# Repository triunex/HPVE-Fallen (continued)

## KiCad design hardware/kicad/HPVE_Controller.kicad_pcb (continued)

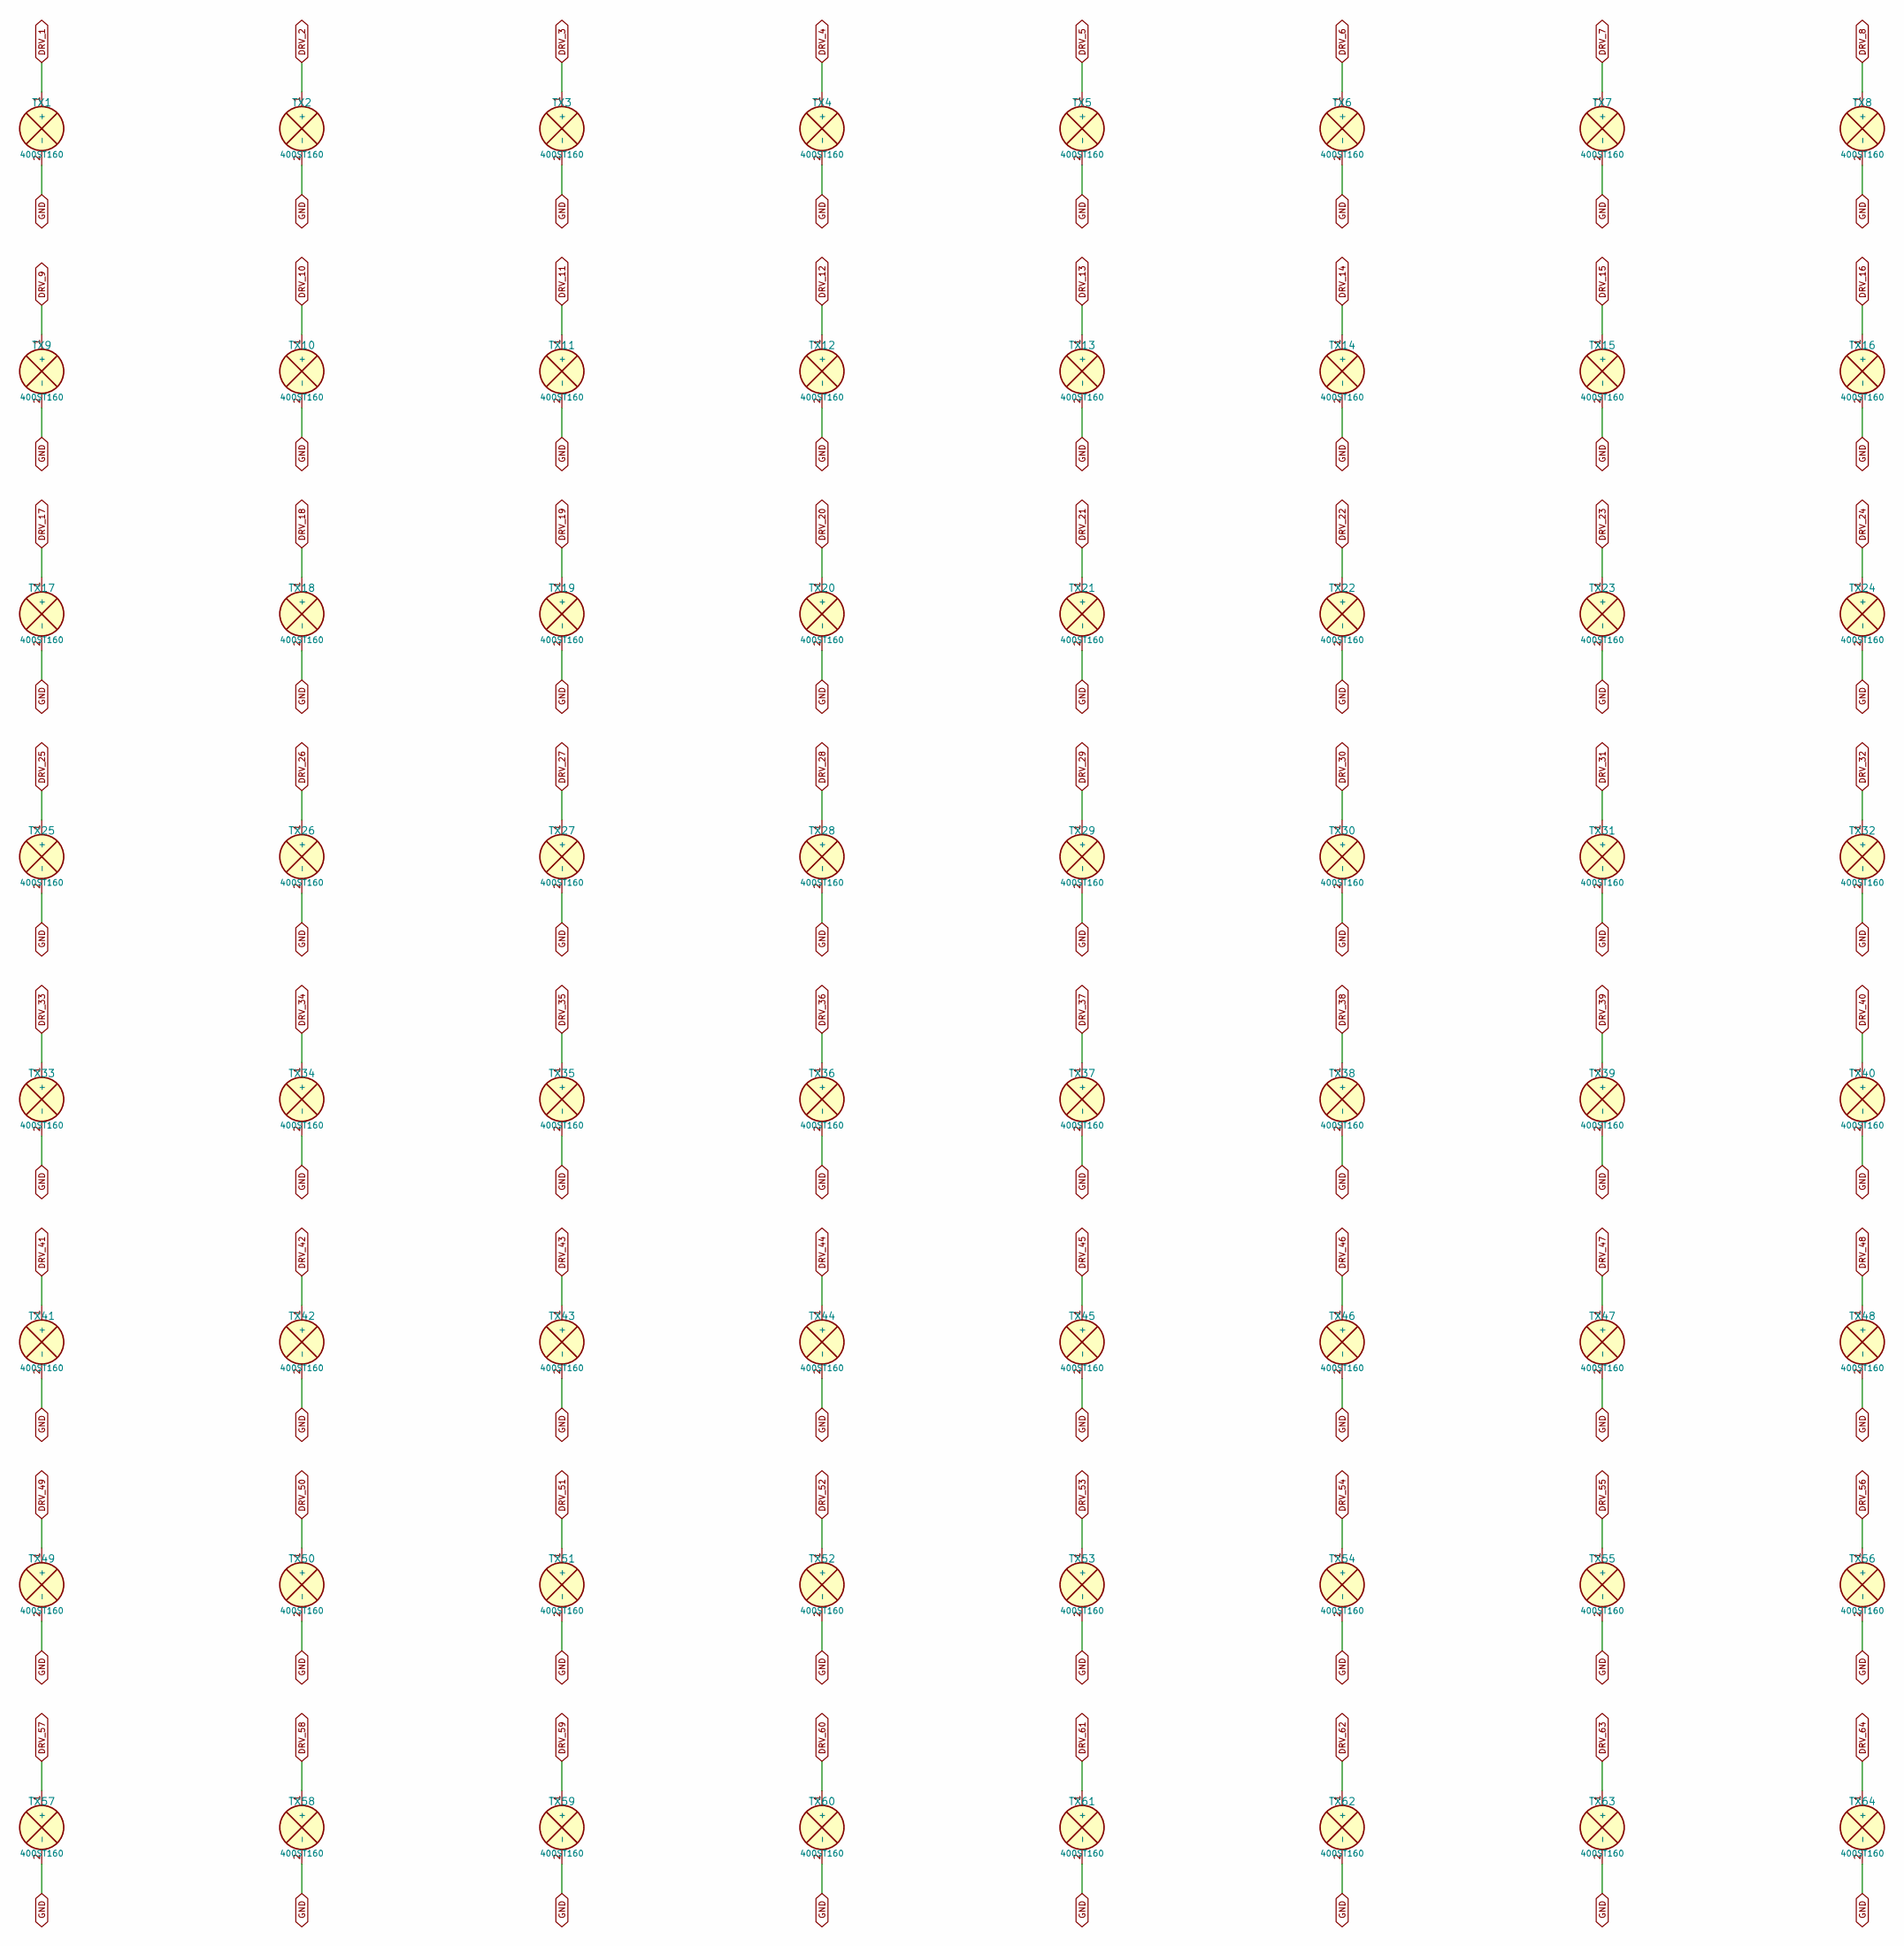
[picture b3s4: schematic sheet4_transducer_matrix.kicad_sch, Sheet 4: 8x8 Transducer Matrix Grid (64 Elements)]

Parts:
TX1, TX2, TX3, TX4, TX5, TX6, TX7, TX8, TX9, TX10, TX11, TX12, TX13, TX14, TX15, TX16, TX17, TX18, TX19, TX20, TX21, TX22, TX23, TX24, TX25, TX26, TX27, TX28, TX29, TX30, TX31, TX32, TX33, TX34, TX35, TX36, TX37, TX38, TX39, TX40, TX41, TX42, TX43, TX44, TX45, TX46, TX47, TX48, TX49, TX50, TX51, TX52, TX53, TX54, TX55, TX56, TX57, TX58, TX59, TX60, TX61, TX62, TX63, TX64: 400ST160; PinHeader_1x02_P2.54mm_Vertical

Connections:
DRV_1: TX1.1 (+); also elsewhere on the board
DRV_2: TX2.1 (+); also elsewhere on the board
DRV_3: TX3.1 (+); also elsewhere on the board
DRV_4: TX4.1 (+); also elsewhere on the board
DRV_5: TX5.1 (+); also elsewhere on the board
DRV_6: TX6.1 (+); also elsewhere on the board
DRV_7: TX7.1 (+); also elsewhere on the board
DRV_8: TX8.1 (+); also elsewhere on the board
DRV_9: TX9.1 (+); also elsewhere on the board
DRV_10: TX10.1 (+); also elsewhere on the board
DRV_11: TX11.1 (+); also elsewhere on the board
DRV_12: TX12.1 (+); also elsewhere on the board
DRV_13: TX13.1 (+); also elsewhere on the board
DRV_14: TX14.1 (+); also elsewhere on the board
DRV_15: TX15.1 (+); also elsewhere on the board
DRV_16: TX16.1 (+); also elsewhere on the board
DRV_17: TX17.1 (+); also elsewhere on the board
DRV_18: TX18.1 (+); also elsewhere on the board
DRV_19: TX19.1 (+); also elsewhere on the board
DRV_20: TX20.1 (+); also elsewhere on the board
DRV_21: TX21.1 (+); also elsewhere on the board
DRV_22: TX22.1 (+); also elsewhere on the board
DRV_23: TX23.1 (+); also elsewhere on the board
DRV_24: TX24.1 (+); also elsewhere on the board
DRV_25: TX25.1 (+); also elsewhere on the board
DRV_26: TX26.1 (+); also elsewhere on the board
DRV_27: TX27.1 (+); also elsewhere on the board
DRV_28: TX28.1 (+); also elsewhere on the board
DRV_29: TX29.1 (+); also elsewhere on the board
DRV_30: TX30.1 (+); also elsewhere on the board
DRV_31: TX31.1 (+); also elsewhere on the board
DRV_32: TX32.1 (+); also elsewhere on the board
DRV_33: TX33.1 (+); also elsewhere on the board
DRV_34: TX34.1 (+); also elsewhere on the board
DRV_35: TX35.1 (+); also elsewhere on the board
DRV_36: TX36.1 (+); also elsewhere on the board
DRV_37: TX37.1 (+); also elsewhere on the board
DRV_38: TX38.1 (+); also elsewhere on the board
DRV_39: TX39.1 (+); also elsewhere on the board
DRV_40: TX40.1 (+); also elsewhere on the board
DRV_41: TX41.1 (+); also elsewhere on the board
DRV_42: TX42.1 (+); also elsewhere on the board
DRV_43: TX43.1 (+); also elsewhere on the board
DRV_44: TX44.1 (+); also elsewhere on the board
DRV_45: TX45.1 (+); also elsewhere on the board
DRV_46: TX46.1 (+); also elsewhere on the board
DRV_47: TX47.1 (+); also elsewhere on the board
DRV_48: TX48.1 (+); also elsewhere on the board
DRV_49: TX49.1 (+); also elsewhere on the board
DRV_50: TX50.1 (+); also elsewhere on the board
DRV_51: TX51.1 (+); also elsewhere on the board
DRV_52: TX52.1 (+); also elsewhere on the board
DRV_53: TX53.1 (+); also elsewhere on the board
DRV_54: TX54.1 (+); also elsewhere on the board
DRV_55: TX55.1 (+); also elsewhere on the board
DRV_56: TX56.1 (+); also elsewhere on the board
DRV_57: TX57.1 (+); also elsewhere on the board
DRV_58: TX58.1 (+); also elsewhere on the board
DRV_59: TX59.1 (+); also elsewhere on the board
DRV_60: TX60.1 (+); also elsewhere on the board
DRV_61: TX61.1 (+); also elsewhere on the board
DRV_62: TX62.1 (+); also elsewhere on the board
DRV_63: TX63.1 (+); also elsewhere on the board
DRV_64: TX64.1 (+); also elsewhere on the board
GND: TX1.2 (-), TX2.2 (-), TX3.2 (-), TX4.2 (-), TX5.2 (-), TX6.2 (-), TX7.2 (-), TX8.2 (-), TX9.2 (-), TX10.2 (-), TX11.2 (-), TX12.2 (-), TX13.2 (-), TX14.2 (-), TX15.2 (-), TX16.2 (-), TX17.2 (-), TX18.2 (-), TX19.2 (-), TX20.2 (-), TX21.2 (-), TX22.2 (-), TX23.2 (-), TX24.2 (-), TX25.2 (-), TX26.2 (-), TX27.2 (-), TX28.2 (-), TX29.2 (-), TX30.2 (-), TX31.2 (-), TX32.2 (-), TX33.2 (-), TX34.2 (-), TX35.2 (-), TX36.2 (-), TX37.2 (-), TX38.2 (-), TX39.2 (-), TX40.2 (-), TX41.2 (-), TX42.2 (-), TX43.2 (-), TX44.2 (-), TX45.2 (-), TX46.2 (-), TX47.2 (-), TX48.2 (-), TX49.2 (-), TX50.2 (-), TX51.2 (-), TX52.2 (-), TX53.2 (-), TX54.2 (-), TX55.2 (-), TX56.2 (-), TX57.2 (-), TX58.2 (-), TX59.2 (-), TX60.2 (-), TX61.2 (-), TX62.2 (-), TX63.2 (-), TX64.2 (-); also elsewhere on the board

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
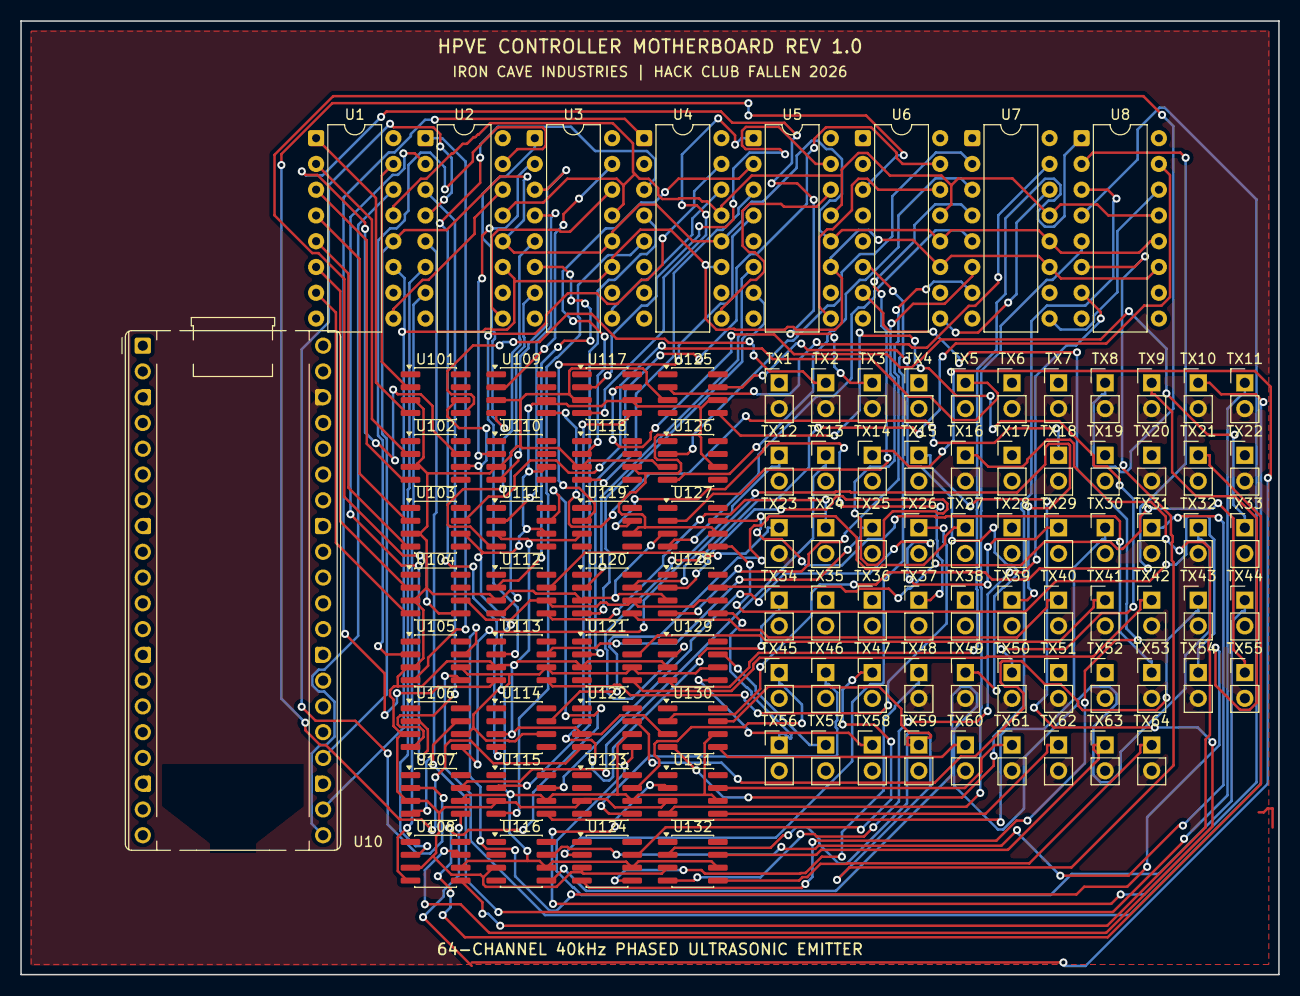
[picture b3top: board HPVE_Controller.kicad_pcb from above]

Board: 2 copper layers, 124.0 x 94.0 mm, 105 parts (0 on the bottom side), 142 nets.

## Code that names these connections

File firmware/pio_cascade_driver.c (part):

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/*
 * Exact Hardware Netlist Mapping for HPVE_Tile_16Ch:
 * - Each tile has 2x 74HC595:
 *   U1 (receives J_IN Pin 4 SPI_MOSI_IN): Q0..Q7 -> SIG_1..SIG_8   -> TX1..TX8
 *   U2 (receives U1 Pin 9 QH' cascade):   Q0..Q7 -> SIG_9..SIG_16  -> TX9..TX16
 *   U2 Pin 9 QH' -> J_OUT Pin 4 SPI_MOSI_OUT -> next tile J_IN Pin 4.
 *
 * - In a 4-tile daisy chain (Tile 0 -> Tile 1 -> Tile 2 -> Tile 3):
 *   64 clock pulses per slice shift 64 bits out of PIO MSB-first (two 32-bit OSR words).
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    gpio_set_dir(PIN_DRV_OE, GPIO_OUT);
    gpio_put(PIN_DRV_OE, 1);

    gpio_init(PIN_SYNC_TRIG);
    gpio_set_dir(PIN_SYNC_TRIG, GPIO_OUT);
    gpio_put(PIN_SYNC_TRIG, 0);

    gpio_init(PIN_STATUS_LED);
    gpio_set_dir(PIN_STATUS_LED, GPIO_OUT);
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        g_pio_inst,
        g_pio_sm,
        g_pio_offset,
        PIN_SPI_MOSI,
        PIN_SPI_SCK,
        clkdiv,
        shift_bits,
        pad_cycles
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
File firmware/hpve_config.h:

#ifndef HPVE_CONFIG_H
#define HPVE_CONFIG_H

#include <stdint.h>
#include <stdbool.h>
#include <stddef.h>

#ifdef __cplusplus
extern "C" {
#endif

#define HPVE_FW_VERSION_MAJOR       2
#define HPVE_FW_VERSION_MINOR       7
#define HPVE_FW_VERSION_PATCH       0

#define SYS_CLOCK_KHZ               128000u
#define SYS_CLOCK_HZ                128000000u
#define PIO_CLKDIV_INT              1u
#define PIO_CLKDIV_FRAC             64u
#define PIO_CLOCK_HZ                102400000u

#define ACOUSTIC_CARRIER_HZ         40000u
#define ACOUSTIC_PERIOD_US          25u
#define SOUND_SPEED_MPS             343.0f
#define ACOUSTIC_WAVELENGTH_M       0.008575f
#define ACOUSTIC_WAVENUMBER_K       732.73298f

#define TILE_GRID_COLS              4u
#define TILE_GRID_ROWS              4u
#define TILE_CHANNELS               16u
#define MAX_CASCADE_TILES           4u
#define NUM_TRANSDUCERS             (TILE_CHANNELS * MAX_CASCADE_TILES)
#define GLOBAL_GRID_COLS            8u
#define GLOBAL_GRID_ROWS            8u

#define TRANSDUCER_PITCH_M          0.0165f
#define TRANSDUCER_CAN_DIAM_M       0.0162f
#define TRANSDUCER_LEAD_PITCH_M     0.0100f
#define TILE_SPAN_M                 (TILE_GRID_COLS * TRANSDUCER_PITCH_M)
#define ARRAY_SPAN_X_M              (GLOBAL_GRID_COLS * TRANSDUCER_PITCH_M)
#define ARRAY_SPAN_Y_M              (GLOBAL_GRID_ROWS * TRANSDUCER_PITCH_M)

#define NUM_PHASE_STEPS             16u
#define PHASE_STEP_MASK             (NUM_PHASE_STEPS - 1u)
#define WORDS_PER_SLICE             2u
#define SLICES_PER_CARRIER_PERIOD   NUM_PHASE_STEPS
#define CARRIER_CYCLES_PER_FRAME    200u
#define SLICES_PER_DMA_FRAME        (SLICES_PER_CARRIER_PERIOD * CARRIER_CYCLES_PER_FRAME)
#define WORDS_PER_DMA_FRAME         (SLICES_PER_DMA_FRAME * WORDS_PER_SLICE)

#define PIO_CYCLES_PER_CARRIER      2560u
#define PIO_CYCLES_PER_SLICE        (PIO_CYCLES_PER_CARRIER / NUM_PHASE_STEPS)
#define PIO_SHIFT_BITS_PER_SLICE    64u

#define HAPTIC_MOD_FREQ_HZ          200u
#define HAPTIC_CARRIER_RATIO        (ACOUSTIC_CARRIER_HZ / HAPTIC_MOD_FREQ_HZ)

#define MAX_MULTIFOCAL_NODES        7u
#define TRAJ_HISTORY_LEN            32u

#define PIN_I2C_SDA                 0u
#define PIN_I2C_SCL                 1u
#define PIN_SPI_MOSI                2u
#define PIN_SPI_SCK                 3u
#define PIN_SPI_LATCH               4u
#define PIN_DRV_OE                  5u
#define PIN_PHOTONIC_R              6u
#define PIN_PHOTONIC_G              7u
#define PIN_PHOTONIC_B              8u
#define PIN_SYNC_TRIG               9u
#define PIN_ENC_X_A                 10u
#define PIN_ENC_X_B                 11u
#define PIN_ENC_Y_A                 12u
#define PIN_ENC_Y_B                 13u
#define PIN_ENC_Z_A                 14u
#define PIN_ENC_Z_B                 15u
#define PIN_BTN_MODE                16u
#define PIN_BTN_ENABLE              17u
#define PIN_STATUS_LED              25u

#define WORKSPACE_MIN_X_M          -0.060f
#define WORKSPACE_MAX_X_M           0.060f
#define WORKSPACE_MIN_Y_M          -0.060f
#define WORKSPACE_MAX_Y_M           0.060f
#define WORKSPACE_MIN_Z_M           0.015f
#define WORKSPACE_MAX_Z_M           0.140f
#define WORKSPACE_DEFAULT_Z_M       0.055f

#define Q16_SHIFT                   16
#define Q16_ONE                     (1 << Q16_SHIFT)
#define Q16_HALF                    (1 << (Q16_SHIFT - 1))
#define FLOAT_TO_Q16(x)             ((int32_t)((x) * (float)Q16_ONE))
#define Q16_TO_FLOAT(x)             ((float)(x) / (float)Q16_ONE)
#define Q16_MUL(a, b)               ((int32_t)(((int64_t)(a) * (int64_t)(b)) >> Q16_SHIFT))
#define Q16_DIV(a, b)               ((int32_t)((((int64_t)(a)) << Q16_SHIFT) / (b)))

typedef int32_t q16_t;

typedef enum {
    HPVE_MODE_STANDBY         = 0,
    HPVE_MODE_TWIN_TRAP       = 1,
    HPVE_MODE_BOTTLE_TRAP     = 2,
    HPVE_MODE_VORTEX_BEAM     = 3,
    HPVE_MODE_HAPTIC_FOCUS    = 4,
    HPVE_MODE_VOLUMETRIC_POV  = 5,
    HPVE_MODE_DUAL_TRAP_SMF   = 6,
    HPVE_MODE_ARC_REACTOR_SMF = 7,
    HPVE_MODE_COUNT           = 8
} hpve_mode_t;

typedef enum {
    TRAJ_NONE_STATIC            = 0,
    TRAJ_ARC_REACTOR_CORE       = 1,
    TRAJ_ENDGAME_MOEBIUS        = 2,
    TRAJ_TREFOIL_KNOT           = 3,
    TRAJ_LISSAJOUS_RIBBON       = 4,
    TRAJ_HAPTIC_FORCEFIELD_WALL = 5,
    TRAJ_HAPTIC_DETENT_DIAL     = 6,
    TRAJ_HELIX_DOUBLE_STRAND    = 7,
    TRAJ_COUNT                  = 8
} hpve_trajectory_type_t;

typedef enum {
    TWIN_AXIS_X               = 0,
    TWIN_AXIS_Y               = 1,
    TWIN_AXIS_DIAGONAL        = 2,
    TWIN_AXIS_QUADRUPOLE      = 3
} hpve_twin_axis_t;

typedef struct {
    float x;
    float y;
    float z;
} vec3f_t;

typedef struct {
    q16_t x;
    q16_t y;
    q16_t z;
} vec3q16_t;

typedef struct {
    uint8_t  tile_id;
    uint8_t  local_ch;
    uint8_t  sr_chip;
    uint8_t  sr_pin_q;
    uint8_t  global_col;
    uint8_t  global_row;
    uint8_t  cascade_bit_pos;
    float    pos_x_m;
    float    pos_y_m;
    q16_t    pos_x_q16;
    q16_t    pos_y_q16;
    int8_t   phase_trim_steps;
} hpve_transducer_map_t;

typedef struct {
    uint8_t  phase_step[NUM_TRANSDUCERS];
    uint8_t  duty_steps[NUM_TRANSDUCERS];
    uint64_t active_mask;
    uint8_t  haptic_am_depth;
    uint8_t  r_pwm;
    uint8_t  g_pwm;
    uint8_t  b_pwm;
} hpve_channel_frame_t;

typedef struct {
    vec3f_t  primary_pos;
    vec3f_t  secondary_pos;
    vec3f_t  velocity_mps;
    float    speed_mps;
    float    curvature_inv_m;
    float    param_u_rad;
    float    param_v_m;
    uint8_t  num_active_nodes;
    vec3f_t  multifocal_nodes[MAX_MULTIFOCAL_NODES];
    float    multifocal_weights[MAX_MULTIFOCAL_NODES];
    uint8_t  multifocal_topological_sign[MAX_MULTIFOCAL_NODES];
    uint8_t  haptic_am_override;
    uint8_t  duty_step_override;
    uint8_t  r_pwm;
    uint8_t  g_pwm;
    uint8_t  b_pwm;
    bool     laser_blank_active;
} hpve_trajectory_sample_t;

typedef struct {
    volatile vec3f_t                focus_primary;
    volatile vec3f_t                focus_secondary;
    volatile hpve_mode_t            active_mode;
    volatile hpve_trajectory_type_t active_trajectory;
    volatile hpve_twin_axis_t       twin_axis;
    volatile int8_t                 vortex_charge;
    volatile float                  bottle_radius_m;
    volatile float                  haptic_mod_hz;
    volatile float                  orbit_radius_m;
    volatile float                  orbit_freq_hz;
    volatile float                  traj_scale;
    volatile float                  traj_yaw_rad;
    volatile float                  traj_pitch_rad;
    volatile float                  moebius_strip_width_m;
    volatile float                  forcefield_z_wall_m;
    volatile float                  finger_probe_z_m;
    volatile bool                   orbit_enabled;
    volatile bool                   output_enabled;
    volatile bool                   use_fixed_point_solver;
    volatile uint32_t               frame_counter;
    volatile uint32_t               dma_swap_counter;
    volatile uint32_t               dma_underrun_counter;
    volatile uint32_t               solver_time_us;
    volatile uint32_t               compile_time_us;
} hpve_system_state_t;

#ifdef __cplusplus
}
#endif

#endif
